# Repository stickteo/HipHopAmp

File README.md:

# HipHopAmp
Opamp based headphone amplifier build project.

# Introduction
This project is divided into five parts:
- Main Amplifier circuit
- Voltage Divider circuit
- LED Music Visualizer
- Circuit Routing & Soldering
- Case Design and 3D Print

I wanted to make a headphone amplifier. The choice to use opamps was due to its simplicity and not needing to use any extra heatsinks.

# Circuit Design
I was inspired by ESP's Portable Amplifier article. I really like the simplicity of using opamps to drive headphones directly. I did build the crossfeed circuit... However, I just prefer not having crossfeed. Thus the final circuit simply involves volume adjustment, using a dual opamp to buffer the input then two dual opamps to drive the output.

## Main Circuit

The circuit is quite simple. The first opamp buffers and amplifies the input by 3 times. The second and third provides the necessary current to output to the headphone.

I didn't show the potentiometer in the circuit. However, R1 and R2 work together with the potentiometer to provide a more logarithmic volume adjustment. Without the resistors, the potentiometer would adjust the volume linearly. Having the resitors in parallel means having more range for quieter volumes.

I kept C1 and C2 so it can block any potential DC. I'm not entirely sure the purpose of R11 and R12.

R3, R5, R4, and R6 sets the overall gain. Without gain, the amplier would only work as a current buffer.

The arrangement of U2 and U3 is very interesting. U2 takes the feedback from the output while U3 acts as a buffer for the output from U3. To have more current, a potential U4 can also act as another buffer like U3.

Aside from the potential to add another buffer, the arrangement makes routing easier as well. This means the opamps can be lined up in a single line while the left and right channels can run on each side. This also means the power rails can be kept in a single line in the center.

## Trying to get a negative rail.
I was again inspired by ESP's article explaining how to use a boost converter to generate 24V and using 12V as ground.

I tried all sorts of configurations:
- Using the MC34063A to create -12V.
- Using 5V to generate 12V and 24V using two MT3608 boost converters.
- Using 12V to generate 24V using one MT3608 boost converter.
- Using LM317 to make it less noisy.

Only the third configuration worked. Though quite disappointingly noisy.

### MC34063A
So I found this IC inside a USB charger that plugs into a car's "cigarette lighter". Essentially the adapter takes in 12V and spits out 5V.

The MC34063A is a control IC that can step-up, step-down, and invert voltages.

I try to build a circuit with it but I ended up blowing up the chip. I think I didn't have the right inductor to properly use it. Building a switching supply can have all sorts of pitfalls. Though it's something I have to try again. Well, it was a bit too complicated and I just wanted a headphone amplifier.

### MT3608
Since trying to build a switching regulator failed, I turned my attention to cheap Chinese boost converters. The MT3608 seemed fairly small and compact.

#### 24V Boost
At first I simply try using the MT3608 to output 24V directly. There's always some weird noise even with a bench supply. I assume the regulator doesn't perform well when there's not much load. Seemingly the MT3608 picks up noise from its input power pin. It's also sensitive to output capacitance as well.

I was trying a range of output capacitors to try to smooth the ripples away... Generally, more output capacitance makes the ripple have a lower frequency while less capacitance (nothing) increases the frequency. Presumably it depends on the control circuit inside the IC. I would guess it's a comparator with some sort of hysteresis.

I used an earbud to check the noise with no input. (Earbuds are more sensistive to noise compared to "audiophile" headphones.) It was tolerable with a bench supply feeding the MT308 to boost to 24V. (12V from the bench supply acts as ground.) When switching to an off the shelf 12V AC-DC adapter the noise got way worse.

#### 5V to 12V and 24V Boost
Using two MT3608 modules to get 12V and 24V from a single 5V supply doesn't work.

The 5V goes to the input of both modules. With no load, 12V and 24V outputs. However, when I connect earbuds on the output, the 12V output would slowly rise to 24V minus a diode drop.

My best guess is that the MT3608 can't sink current. Presumably if the output sees a higher voltage than what is set, then the output transistor will not turn on. I can only guess the diode drop comes from the output of the opamp. (Since the 4558 opamp is not rail-to-rail.) Thus the output pours current into the 12V line and into the capacitors. Perhaps the slow rise is due to small currents flowing through the headphone. Thus the MT3608 can't regulate any voltages higher than its set point.

There needs to be further testing. Perhaps just using a bench supply at 24V and setting the MT3608 to output 12V using 5V input. Then simply connecting a resistor from 24V to the 12V output. Overall though, the MT3608 is not a good application for generating intermediate voltages.

#### Using LM317 to generate 24V
As a last ditch effort, I try using the LM317 to create a 24V line while using the MT3608 set at 27V. It works okay with a bench supply providing 12V. However, using an AC adapter to provide 12V results in a lot of noise.

Opamps do reject supply noise. However, noise on ground would render it worthless since the opamp only sees 0V and 24V on its negative and positive supply pins. Thus the noise would appear on the inputs. Of course, the 12V input should be regulated as well... Perhaps with another LM317. However, this would make the project overly complicated and too bulky.

## Voltage Divider Circuit

Of course, the circuit is completely taken from an ESP article.

The circuit is really simple. Two RC circuits in series to create a stable voltage divider. Using that stable voltage, the opamp would buffer the voltage creating a new stable middle voltage.

With the way the schematic is drawn, it's a little misleading that one pushes and the other pulls current. In actuality, using two opamp means doubling the amount of current available to supply to the new rail. Since the 4558 is a dual opamp, might as well as use both.

# LED Music Visualizer

A certain special person wanted blinky lights, so I added blinky lights.

I wanted something simple and compact... Thus came brainstorming ideas...

A complex idea is to throw an Arduino Nano at the problem. Get the Nano to read the audio through its analog pins... Do some sort of processing... Then simply output to an LED. However, I don't think it really fits the "theme" of my project.

Thus I search online something like "Audio LED" then came across an Instructables project. It's really simple, simply let an audio signal input into an NPN BJT to control an LED. Very "basic" stuff but some details have to be correct.

So, I just start breadboarding the circuit.

## Instructables BJT LED Driver

It's really straight forward... But a little too simple for comfort. It definitely works and the BJT will go into saturation. Although the base is commonly conceptualized as a switch with a small current, a more accurate view is a diode instead. The base and the emmitter is literally a diode junction. Without a base resistor, large amounts of current will flow from the base to the emmiter whenever a voltage higher than 0.7V is applied.

By tapping the input with a bench supply, I would see several hundreds of milliamps being drawn. I suppose as long as the BJT doesn't get too hot, it would release the magic smoke... But yeah, the things you only "really" learn by purely building the circuit and not from reading a textbook.

From there, I added a base resistor and tested with audio... It seemed a bit lacking and not bright enough.

## Voltage Offset
In my circuit, R5 and R6 form a voltage divider to set the offset to Q2. This offset should be just below a diode drop. With those values, around 0.5V. If it's too high, the LED will just stay on. Too low and the LED will blink too briefly and not as bright.

A bad point about this is that it depends a lot on the 12V supply. ACDC adapters can have wide output... Sometimes around 13V.

Perhaps to make it more supply agnostic I would use a diode with a resistor divider to create the offset instead.

## Voltage Gain Amplifier
I wanted the LEDs to blink more brightly, thus I implement a simple common-emmitter amplifier with emitter degeneration. 

The gain is set by R3 and R4. I tried having max gain by ommitting R4... However, the effect becomes less subtle.

To calculate R1, R2, R3, and R4:
- V_C is VCC/2 which is 6V
- Desired gain, G, is 20
- Desired quiescent current, I_C, is 1~2mA
- R3 = VCC/2/I_C = 6V / 2mA = ~3kOhm
- R4 = R3/G = 3kOhm / 20 = ~150Ohm
- V_E = R4*I_C = 150Ohm * 2mA = ~0.3V
- V_B = V_E + 0.6V = 0.3V + 0.6V = ~0.9V
- I_B = I_C/10 = 2mA / 10 = 0.2mA
- R2 = V_B/I_B = 0.9V / 0.2mA = ~4.5kOhm
- R1 = (VCC-V_B)/I_B = 11.1V / 0.2mA = ~55.5kOhm

I try to choose convenient values for the actual circuit. Resistances can be slighly lowered to a more convenient value.

# Circuit Routing

I want the circuit to be easily assembled by hand soldering. This meant using through-hole components. A big aspect is minimizing the amount of soldering done and using minimal amount of links.

Using KiCad to draw the schematic and route avoids making a lot of mistakes. I make sure to render in 3D to not make the mistake of flipping the IC to the wrong side. (It does happen.)

I use a perforated board to construct the circuit. This simply means setting 0.1in spacing inside KiCad and routing. As you can see in the images, everything is tightly packed together. Multiple iterations are made... Rotating resistors in one way... Rotating it in another way.

Several goals under consideration:
- Ease of construction
- Minimize traces
- Minimize area
- Minimize bridges

Having the schematic and routing up makes it easy to double-check components while soldering them in.

Capacitors are forgiving. We can always use a lower voltage capicitor that can fit. For proper production though, this would not be good for machines to assemble. Though for hand assembly, I am okay with the trade-off to achieve a more compact construction as well as decrease the amount of traces I need to create. I mockup the circuit while routing to make sure everything can fit.

Connectors are really space consuming as well as impose more design limitations. I opt to forgo connectors with direct soldering instead. Having connectors will require more traces to be routed and soldered.

For high-volume production, all parts will need to be SMD. Using a single layer can potentially lower the cost even further. Otherwise having two layers will allow easier routing. The choice of connectors will be especially important.

For DIY, we should allow ourselves the flexibility to use whatever connectors we want or what types of potentiometers we can have. Just soldering a wire is several times easier than trying to crimp custom connectors. Connectors shouldn't be used liberally as they impose a lot of constraints (and costs). Chinese engineering does really build things down to a cost. A lot of tradeoffs must be made to do so.

With the final routing, three wires must be soldered (the blue traces). I wanted to prioritize signal traces over power traces. The wiring will be longer than traces.

# Resources
- ESP Portable Amplifier: https://sound-au.com/project109.htm
- Burr-Brown's AB-051 application note: https://sound-au.com/sboa031.pdf
- ESP Simple DC Adapter Power Supply: https://sound-au.com/project43.htm
- ESP Obtaining +/- Supplies From A Single Power Supply: https://sound-au.com/project192.htm
- CozzBP Audio Reactive LED Circuit: https://www.instructables.com/Creating-An-Audio-Reactive-LED-Circuit/

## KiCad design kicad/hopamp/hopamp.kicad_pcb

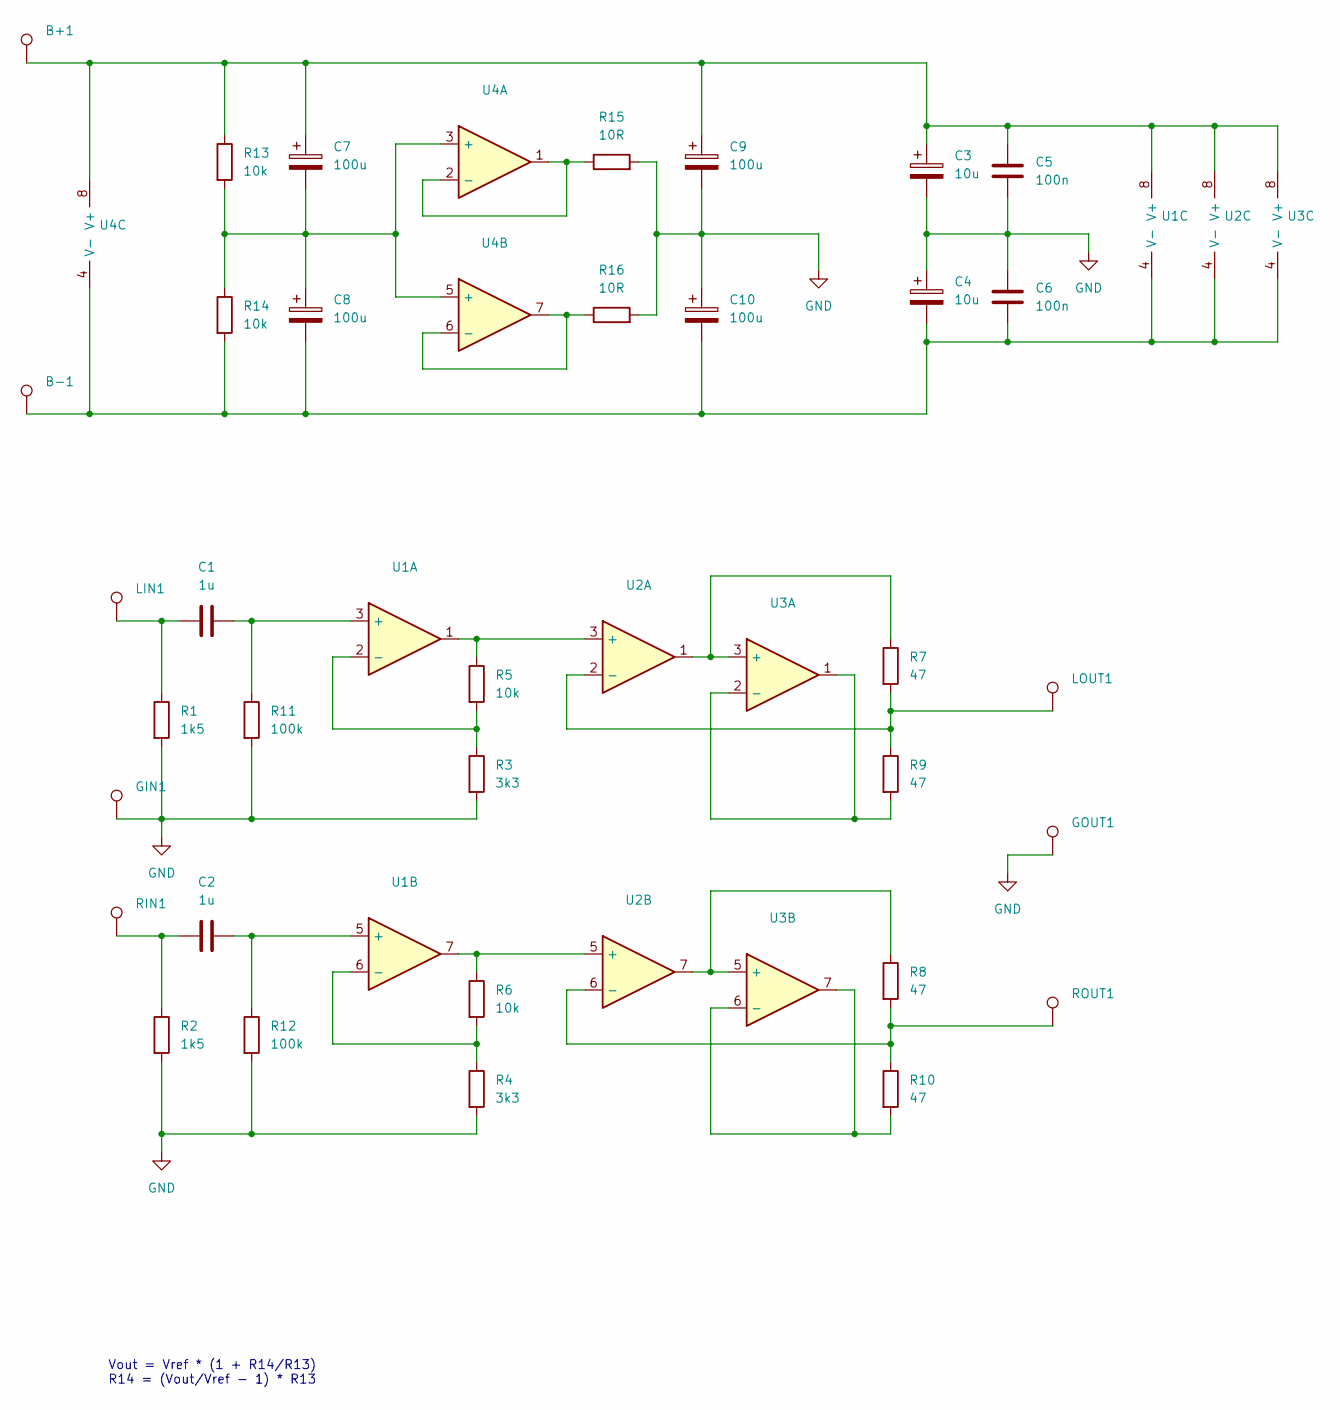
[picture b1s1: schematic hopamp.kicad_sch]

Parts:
B+1: TestPoint; PinHeader_1x01_P2.54mm_Vertical
B-1: TestPoint; PinHeader_1x01_P2.54mm_Vertical
C1, C2: 1u; CP_Radial_D8.0mm_P5.00mm
C3, C4: 10u; CP_Radial_D8.0mm_P5.00mm
C5, C6: 100n; C_Disc_D7.5mm_W4.4mm_P5.00mm
C7, C8, C9, C10: 100u; CP_Radial_D10.0mm_P5.00mm
GIN1: TestPoint; PinHeader_1x01_P2.54mm_Vertical
GOUT1: TestPoint; PinHeader_1x01_P2.54mm_Vertical
LIN1: TestPoint; PinHeader_1x01_P2.54mm_Vertical
LOUT1: TestPoint; PinHeader_1x01_P2.54mm_Vertical
R1, R2: 1k5; R_Axial_DIN0207_L6.3mm_D2.5mm_P10.16mm_Horizontal
R3, R4: 3k3; R_Axial_DIN0207_L6.3mm_D2.5mm_P10.16mm_Horizontal
R5, R6, R13, R14: 10k; R_Axial_DIN0207_L6.3mm_D2.5mm_P10.16mm_Horizontal
R7, R8, R9, R10: 47; R_Axial_DIN0207_L6.3mm_D2.5mm_P10.16mm_Horizontal
R11, R12: 100k; R_Axial_DIN0207_L6.3mm_D2.5mm_P10.16mm_Horizontal
R15, R16: 10R; R_Axial_DIN0207_L6.3mm_D2.5mm_P10.16mm_Horizontal
RIN1: TestPoint; PinHeader_1x01_P2.54mm_Vertical
ROUT1: TestPoint; PinHeader_1x01_P2.54mm_Vertical
U1, U2, U3: Opamp_Dual; DIP-8_W7.62mm_LongPads
U4: Opamp_Dual; DIP-8_W7.62mm_Socket

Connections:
GND: C3.2, C4.1, C5.2, C6.1, C9.2, C10.1, GIN1.1, GOUT1.1, R1.2, R2.2, R3.2, R4.2, R11.2, R12.2, R15.2, R16.2
unnamed: C1.1, LIN1.1, R1.1
unnamed: C2.1, R2.1, RIN1.1
unnamed: C1.2, R11.1, U1.3 (+)
unnamed: R3.1, R5.2, U1.2 (-)
unnamed: C2.2, R12.1, U1.5 (+)
unnamed: R4.1, R6.2, U1.6 (-)
unnamed: B+1.1, C3.1, C5.1, C7.1, C9.1, R13.1, U1.8 (V+), U2.8 (V+), U3.8 (V+), U4.8 (V+)
unnamed: B-1.1, C4.2, C6.2, C8.2, C10.2, R14.2, U1.4 (V-), U2.4 (V-), U3.4 (V-), U4.4 (V-)
unnamed: R5.1, U1.1, U2.3 (+)
unnamed: LOUT1.1, R7.2, R9.1, U2.2 (-)
unnamed: R6.1, U1.7, U2.5 (+)
unnamed: R8.2, R10.1, ROUT1.1, U2.6 (-)
unnamed: R7.1, U2.1, U3.3 (+)
unnamed: R9.2, U3.1, U3.2 (-)
unnamed: R8.1, U2.7, U3.5 (+)
unnamed: R10.2, U3.6 (-), U3.7
unnamed: C7.2, C8.1, R13.2, R14.1, U4.3 (+), U4.5 (+)
unnamed: R15.1, U4.1, U4.2 (-)
unnamed: R16.1, U4.6 (-), U4.7

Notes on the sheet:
Vout = Vref * (1 + R14/R13) R14 = (Vout/Vref - 1) * R13

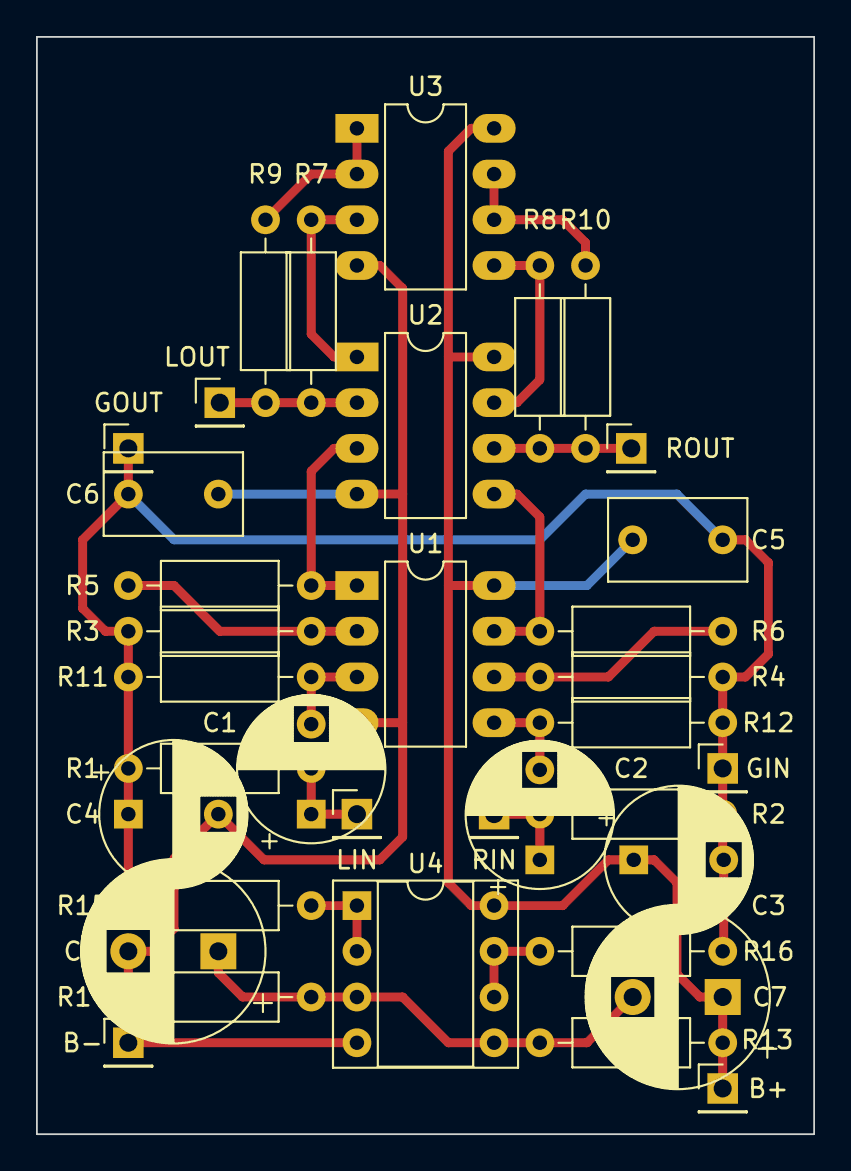
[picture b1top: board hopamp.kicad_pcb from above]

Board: 2 copper layers, 43.2 x 61.0 mm, 36 parts (0 on the bottom side), 20 nets.

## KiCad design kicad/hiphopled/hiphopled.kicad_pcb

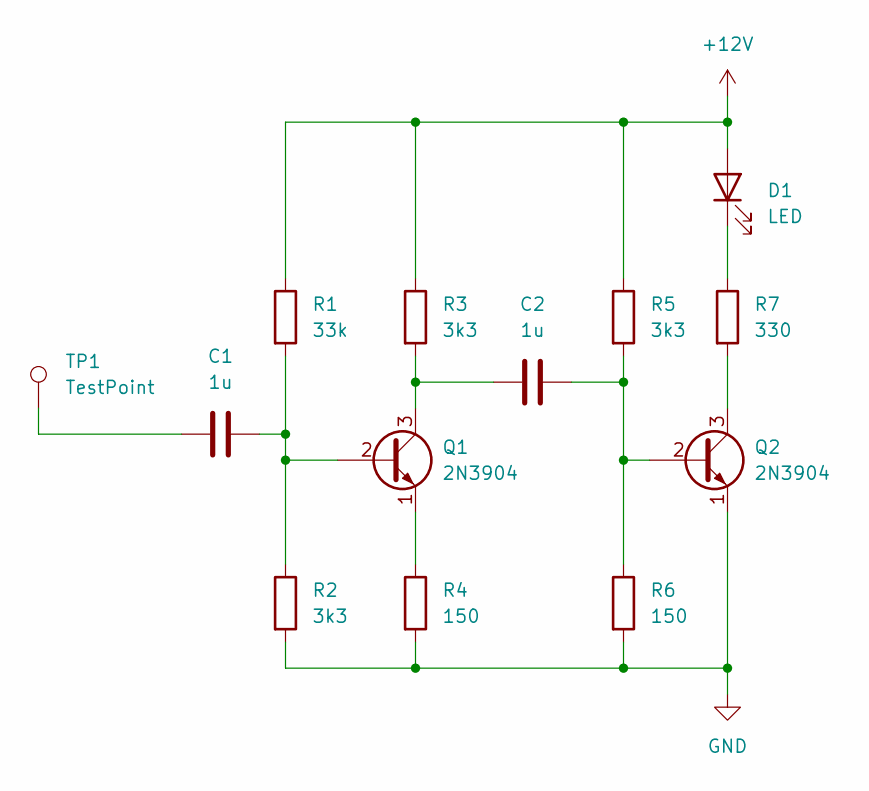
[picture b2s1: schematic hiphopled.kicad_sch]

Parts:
C1, C2: 1u; C_Axial_L3.8mm_D2.6mm_P7.50mm_Horizontal
D1: LED; LED_D8.0mm
Q1, Q2: 2N3904; TO-92L_Wide
R1: 33k; R_Axial_DIN0309_L9.0mm_D3.2mm_P12.70mm_Horizontal
R2, R3, R5: 3k3; R_Axial_DIN0309_L9.0mm_D3.2mm_P12.70mm_Horizontal
R4, R6: 150; R_Axial_DIN0309_L9.0mm_D3.2mm_P12.70mm_Horizontal
R7: 330; R_Axial_DIN0309_L9.0mm_D3.2mm_P12.70mm_Horizontal
TP1: TestPoint; TestPoint_Pad_2.5x2.5mm

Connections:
+12V: D1.2 (A), R1.1, R3.1, R5.1
GND: Q2.1 (E), R2.2, R4.2, R6.2
unnamed: C1.1, TP1.1
unnamed: D1.1 (K), R7.1
unnamed: C1.2, Q1.2 (B), R1.2, R2.1
unnamed: C2.1, Q1.3 (C), R3.2
unnamed: Q1.1 (E), R4.1
unnamed: C2.2, Q2.2 (B), R5.2, R6.1
unnamed: Q2.3 (C), R7.2

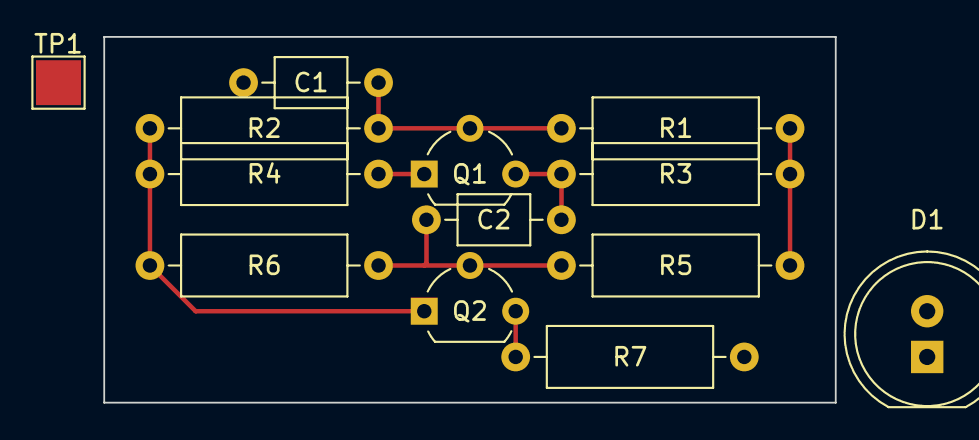
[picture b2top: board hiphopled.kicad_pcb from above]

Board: 2 copper layers, 40.6 x 20.3 mm, 13 parts (0 on the bottom side), 9 nets.

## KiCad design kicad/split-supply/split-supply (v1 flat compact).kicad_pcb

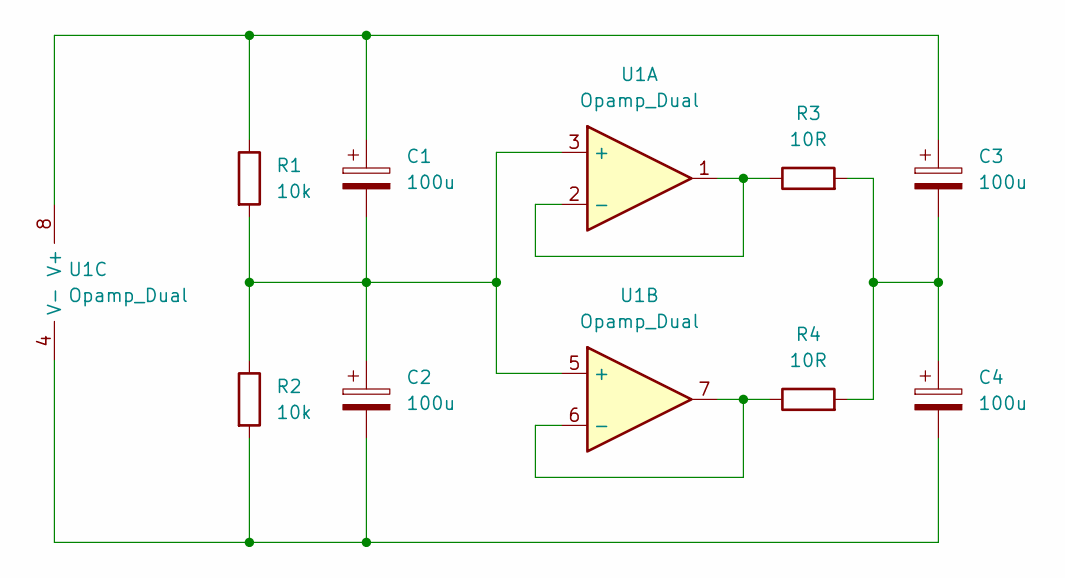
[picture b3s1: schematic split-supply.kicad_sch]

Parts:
C1, C2, C3, C4: 100u; CP_Radial_D10.0mm_P5.00mm
R1, R2: 10k; R_Axial_DIN0204_L3.6mm_D1.6mm_P5.08mm_Vertical
R3, R4: 10R; R_Axial_DIN0204_L3.6mm_D1.6mm_P5.08mm_Vertical
U1: Opamp_Dual; DIP-8_W7.62mm_Socket

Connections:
unnamed: C3.2, C4.1, R3.2, R4.2
unnamed: C1.2, C2.1, R1.2, R2.1, U1.3 (+), U1.5 (+)
unnamed: R3.1, U1.1, U1.2 (-)
unnamed: R4.1, U1.6 (-), U1.7
unnamed: C1.1, C3.1, R1.1, U1.8 (V+)
unnamed: C2.2, C4.2, R2.2, U1.4 (V-)

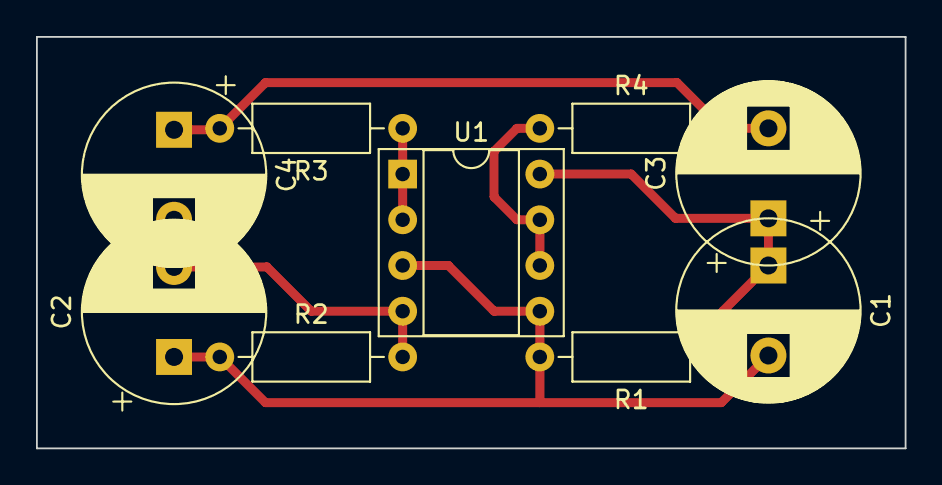
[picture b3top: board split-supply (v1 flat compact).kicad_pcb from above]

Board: 2 copper layers, 48.3 x 22.9 mm, 9 parts (0 on the bottom side), 6 nets.

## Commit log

2024-06-02 Rename circuit-main.png to images/circuit-main.png
2024-06-18 Kicad PCB images.
2024-09-12 KiCad Project Files
2024-11-08 Update with PCB routing
